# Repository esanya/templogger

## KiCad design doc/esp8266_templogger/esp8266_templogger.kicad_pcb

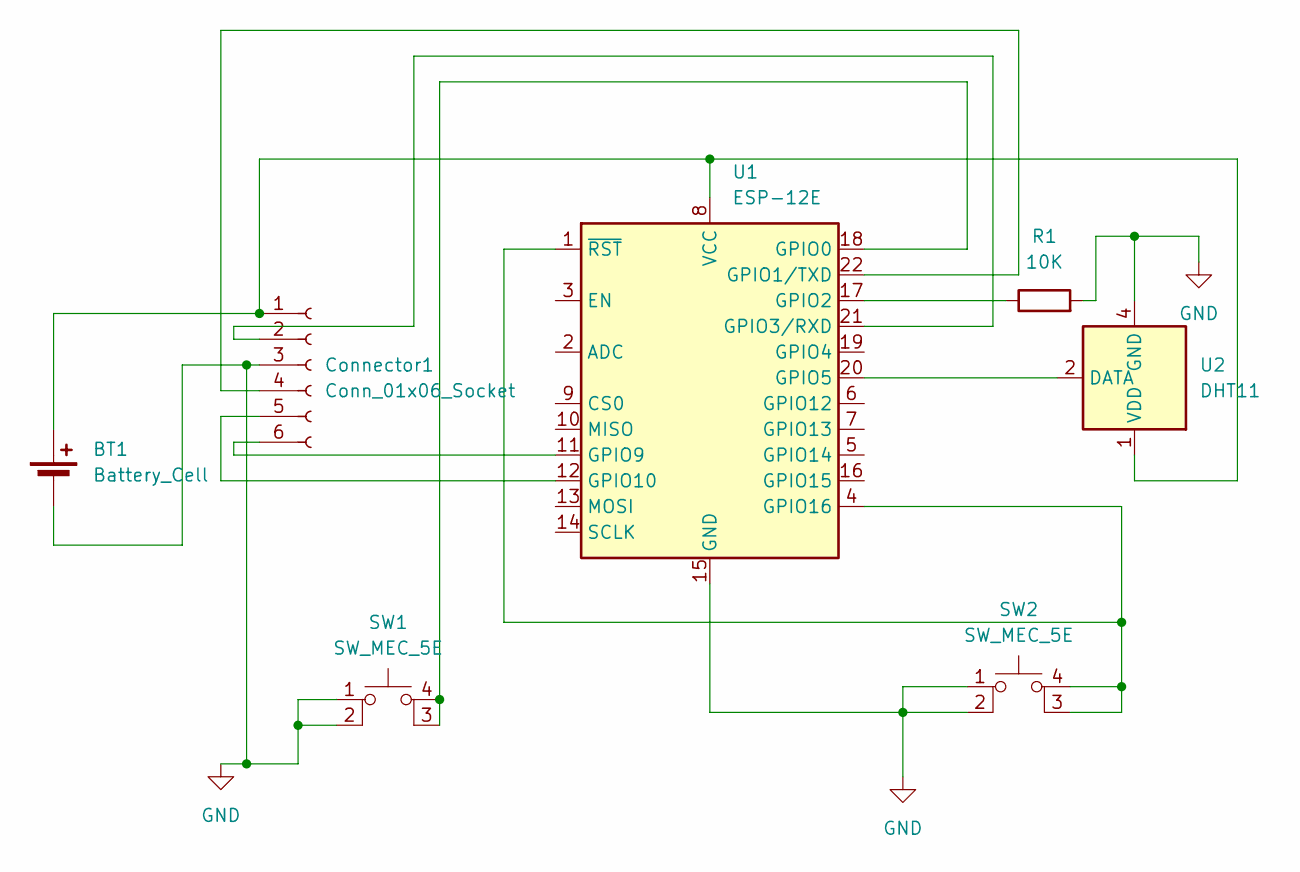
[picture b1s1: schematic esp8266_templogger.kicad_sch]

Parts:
BT1: Battery_Cell; BatteryHolder_Bulgin_BX0123_1xCR123
Connector1: Conn_01x06_Socket; PinHeader_1x06_P2.54mm_Horizontal
R1: 10K; R_Axial_DIN0204_L3.6mm_D1.6mm_P5.08mm_Horizontal
SW1, SW2: SW_MEC_5E; KSA_Tactile_SPST
U1: ESP-12E
U2: DHT11; Aosong_DHT11_5.5x12.0_P2.54mm

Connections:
GND: BT1.2 (-), Connector1.3, R1.2, SW1.1, SW1.2, SW2.1, SW2.2, U1.15 (GND), U2.4 (GND)
unnamed: BT1.1 (+), Connector1.1, U1.8 (VCC), U2.1 (VDD)
unnamed: Connector1.2, U1.21 (GPIO3/RXD)
unnamed: Connector1.4, U1.22 (GPIO1/TXD)
unnamed: Connector1.5, U1.12 (GPIO10)
unnamed: Connector1.6, U1.11 (GPIO9)
unnamed: SW1.3 (K), SW1.4 (A), U1.18 (GPIO0)
unnamed: SW2.3 (K), SW2.4 (A), U1.1 (~RST), U1.4 (GPIO16)
unnamed: R1.1, U1.17 (GPIO2)
unnamed: U1.20 (GPIO5), U2.2 (DATA)

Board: 2 copper layers, 7 parts (0 on the bottom side), 10 nets, no tracks yet.
